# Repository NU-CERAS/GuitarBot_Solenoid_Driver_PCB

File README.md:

KiCAD files for the GuitarBot's Solenoid Driver

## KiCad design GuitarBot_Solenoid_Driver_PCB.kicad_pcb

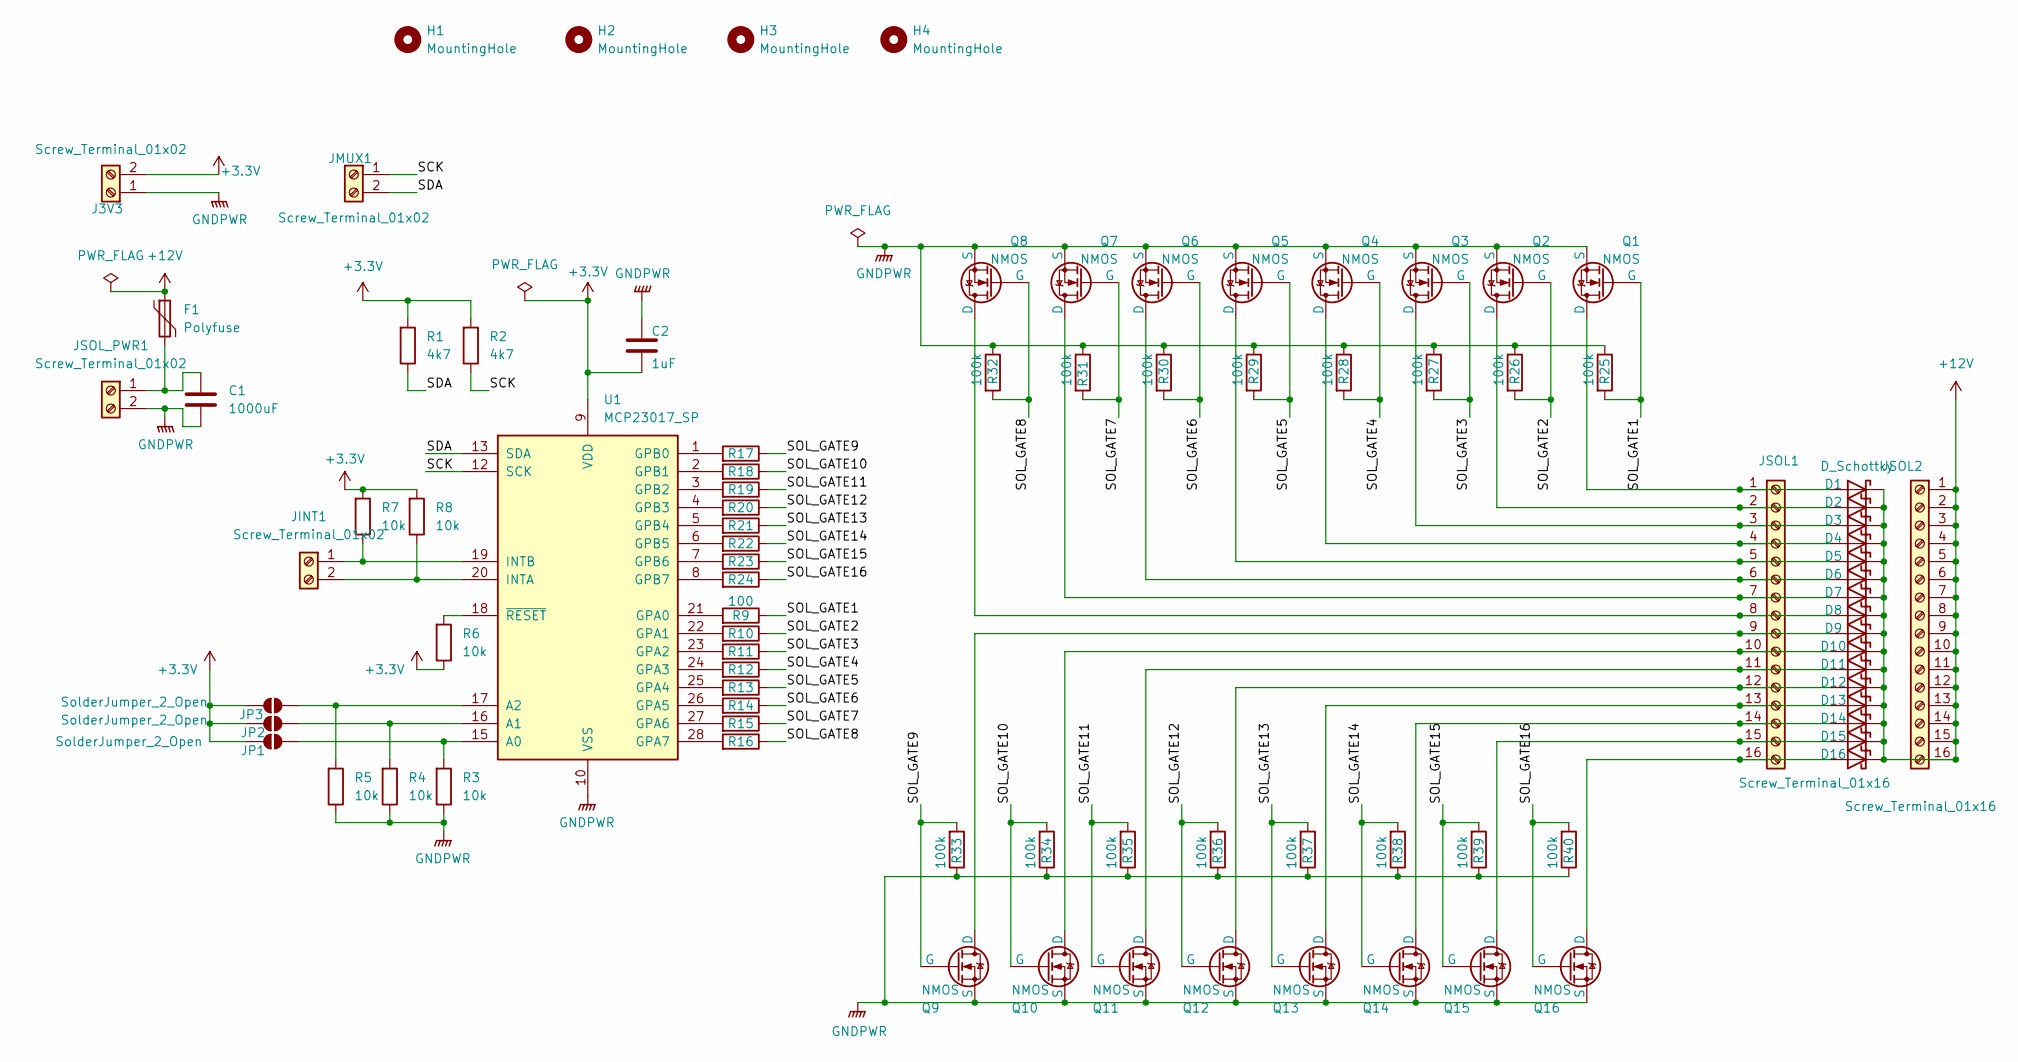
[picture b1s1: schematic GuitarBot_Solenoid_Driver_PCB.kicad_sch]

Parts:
C1: 1000uF; CP_Radial_D10.0mm_P5.00mm
C2: 1uF; C_Radial_D10.0mm_H16.0mm_P5.00mm
D1, D2, D3, D4, D5, D6, D7, D8, D9, D10, D11, D12, D13, D14, D15, D16: D_Schottky; D_DO-201AD_P12.70mm_Horizontal
F1: Polyfuse; C_Disc_D11.0mm_W5.0mm_P5.00mm
H1, H2, H3, H4: MountingHole; MountingHole_3.2mm_M3
J3V3: Screw_Terminal_01x02; TerminalBlock_Xinya_XY308-2.54-2P_1x02_P2.54mm_Horizontal
JINT1: Screw_Terminal_01x02; TerminalBlock_Xinya_XY308-2.54-2P_1x02_P2.54mm_Horizontal
JMUX1: Screw_Terminal_01x02; TerminalBlock_Xinya_XY308-2.54-2P_1x02_P2.54mm_Horizontal
JP1, JP2, JP3: SolderJumper_2_Open; SolderJumper-2_P1.3mm_Open_TrianglePad1.0x1.5mm
JSOL1, JSOL2: Screw_Terminal_01x16; TerminalBlock_CUI_TB007-508-16_1x16_P5.08mm_Horizontal
JSOL_PWR1: Screw_Terminal_01x02; TerminalBlock_MaiXu_MX126-5.0-02P_1x02_P5.00mm
Q1, Q2, Q3, Q4, Q5, Q6, Q7, Q8, Q9, Q10, Q11, Q12, Q13, Q14, Q15, Q16: NMOS; TO-220-3_Vertical
R1, R2: 4k7; R_Axial_DIN0207_L6.3mm_D2.5mm_P7.62mm_Horizontal
R3, R4, R5, R6, R7, R8: 10k; R_Axial_DIN0207_L6.3mm_D2.5mm_P7.62mm_Horizontal
R9, R10, R11, R12, R13, R14, R15, R16, R17, R18, R19, R20, R21, R22, R23, R24: 100; R_Axial_DIN0207_L6.3mm_D2.5mm_P7.62mm_Horizontal
R25, R26, R27, R28, R29, R30, R31, R32, R33, R34, R35, R36, R37, R38, R39, R40: 100k; R_Axial_DIN0207_L6.3mm_D2.5mm_P7.62mm_Horizontal
U1: MCP23017_SP; DIP-28_W7.62mm

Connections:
+3.3V: C2.2, J3V3.2, JP1.1 (A), JP2.1 (A), JP3.1 (A), R1.1, R2.1, R6.2, R7.1, R8.1, U1.9 (VDD)
+12V: D1.1 (K), D2.1 (K), D3.1 (K), D4.1 (K), D5.1 (K), D6.1 (K), D7.1 (K), D8.1 (K), D9.1 (K), D10.1 (K), D11.1 (K), D12.1 (K), D13.1 (K), D14.1 (K), D15.1 (K), D16.1 (K), F1.1, JSOL2.1, JSOL2.2, JSOL2.3, JSOL2.4, JSOL2.5, JSOL2.6, JSOL2.7, JSOL2.8, JSOL2.9, JSOL2.10, JSOL2.11, JSOL2.12, JSOL2.13, JSOL2.14, JSOL2.15, JSOL2.16
/SCK: JMUX1.1, R2.2, U1.12 (SCK)
/SDA: JMUX1.2, R1.2, U1.13 (SDA)
/SOL_GATE1: Q1.1 (G), R9.1, R25.2
/SOL_GATE2: Q2.1 (G), R10.1, R26.2
/SOL_GATE3: Q3.1 (G), R11.1, R27.2
/SOL_GATE4: Q4.1 (G), R12.1, R28.2
/SOL_GATE5: Q5.1 (G), R13.1, R29.2
/SOL_GATE6: Q6.1 (G), R14.1, R30.2
/SOL_GATE7: Q7.1 (G), R15.1, R31.2
/SOL_GATE8: Q8.1 (G), R16.1, R32.2
/SOL_GATE9: Q9.1 (G), R17.1, R33.2
/SOL_GATE10: Q10.1 (G), R18.1, R34.2
/SOL_GATE11: Q11.1 (G), R19.1, R35.2
/SOL_GATE12: Q12.1 (G), R20.1, R36.2
/SOL_GATE13: Q13.1 (G), R21.1, R37.2
/SOL_GATE14: Q14.1 (G), R22.1, R38.2
/SOL_GATE15: Q15.1 (G), R23.1, R39.2
/SOL_GATE16: Q16.1 (G), R24.1, R40.2
GNDPWR: C1.2, C2.1, J3V3.1, JSOL_PWR1.2, Q1.3 (S), Q2.3 (S), Q3.3 (S), Q4.3 (S), Q5.3 (S), Q6.3 (S), Q7.3 (S), Q8.3 (S), Q9.3 (S), Q10.3 (S), Q11.3 (S), Q12.3 (S), Q13.3 (S), Q14.3 (S), Q15.3 (S), Q16.3 (S), R3.2, R4.2, R5.2, R25.1, R26.1, R27.1, R28.1, R29.1, R30.1, R31.1, R32.1, R33.1, R34.1, R35.1, R36.1, R37.1, R38.1, R39.1, R40.1, U1.10 (VSS)
unnamed: D1.2 (A), JSOL1.1, Q1.2 (D)
unnamed: D2.2 (A), JSOL1.2, Q2.2 (D)
unnamed: D3.2 (A), JSOL1.3, Q3.2 (D)
unnamed: D4.2 (A), JSOL1.4, Q4.2 (D)
unnamed: D5.2 (A), JSOL1.5, Q5.2 (D)
unnamed: D6.2 (A), JSOL1.6, Q6.2 (D)
unnamed: D7.2 (A), JSOL1.7, Q7.2 (D)
unnamed: D8.2 (A), JSOL1.8, Q8.2 (D)
unnamed: D9.2 (A), JSOL1.9, Q9.2 (D)
unnamed: D10.2 (A), JSOL1.10, Q10.2 (D)
unnamed: D11.2 (A), JSOL1.11, Q11.2 (D)
unnamed: D12.2 (A), JSOL1.12, Q12.2 (D)
unnamed: D13.2 (A), JSOL1.13, Q13.2 (D)
unnamed: D14.2 (A), JSOL1.14, Q14.2 (D)
unnamed: D15.2 (A), JSOL1.15, Q15.2 (D)
unnamed: D16.2 (A), JSOL1.16, Q16.2 (D)
unnamed: JINT1.1, R7.2, U1.19 (INTB)
unnamed: JINT1.2, R8.2, U1.20 (INTA)
unnamed: JP1.2 (B), R3.1, U1.15 (A0)
unnamed: JP2.2 (B), R4.1, U1.16 (A1)
unnamed: JP3.2 (B), R5.1, U1.17 (A2)
unnamed: C1.1, F1.2, JSOL_PWR1.1
unnamed: R9.2, U1.21 (GPA0)
unnamed: R10.2, U1.22 (GPA1)
unnamed: R11.2, U1.23 (GPA2)
unnamed: R12.2, U1.24 (GPA3)
unnamed: R13.2, U1.25 (GPA4)
unnamed: R14.2, U1.26 (GPA5)
unnamed: R15.2, U1.27 (GPA6)
unnamed: R16.2, U1.28 (GPA7)
unnamed: R17.2, U1.1 (GPB0)
unnamed: R18.2, U1.2 (GPB1)
unnamed: R19.2, U1.3 (GPB2)
unnamed: R20.2, U1.4 (GPB3)
unnamed: R21.2, U1.5 (GPB4)
unnamed: R22.2, U1.6 (GPB5)
unnamed: R23.2, U1.7 (GPB6)
unnamed: R24.2, U1.8 (GPB7)
unnamed: R6.1, U1.18 (~RESET)

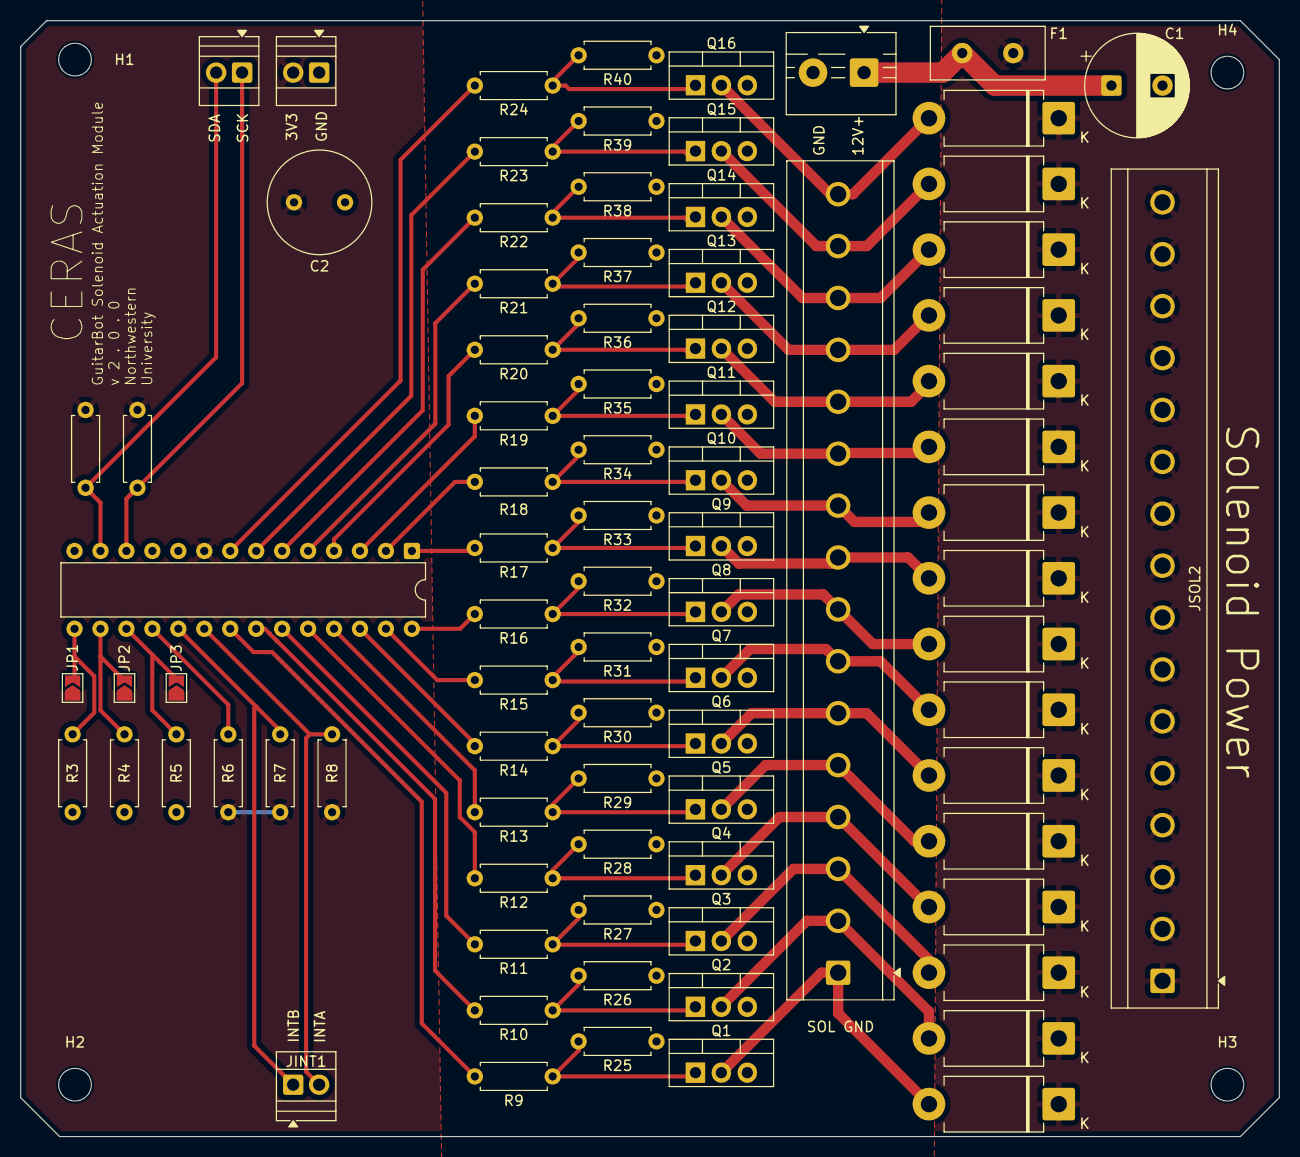
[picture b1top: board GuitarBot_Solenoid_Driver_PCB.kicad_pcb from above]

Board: 2 copper layers, 123.2 x 109.2 mm, 89 parts (0 on the bottom side), 60 nets.

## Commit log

2026-01-06 CMOS schematic complete. Footprints needed
2026-01-11 CMOS array schematic first draft
2026-01-11 modified fp-info-cache
2026-01-18 cmos schematic footprints
2026-01-18 Modified ./old schematic to use NMOS instead of Darlington transistor array
2026-01-29 Added footprints to new board. Switched new and old directories
2026-02-05 Started pcb layout and updated schematic
2026-02-05 Started layout and updated schematic
2026-02-08 Fixed transistors in the schematic and added transistor wiring for PCB
2026-02-12 Fixed NMOS symbol in schematic. Finished wiring the PCB
2026-02-12 cleaned up extra files, added .gitignore
2026-02-12 cleanup
2026-02-15 schematic: interrupt and reset pulldown, NMOS gate pulldown, fuses on 12V and 3V3
2026-02-22 Finished feb15 updates to layout
2026-02-26 made wired farther apart
2026-03-05 initial schematics for ilya rennovations
2026-03-05 Finished up the layout, it passes DRC but idk how good it looks
2026-04-05 Fixed connectection issue with resistors
2026-04-09 Switched to 5.08mm 01x16 terminal blocks
2026-04-09 changed 01x16 terminal blocks from 2.54mm to 5.08mm
2026-04-09 Minimal changes to naming
2026-04-12 Added labelling for inputs and outputs
2026-04-12 Reverted NMOS footprint to 220-3. Rearranged terminalblocks to fit accordingly.
2026-04-12 changed polyfuse footprint
2026-04-12 fixed labels:
2026-04-16 fixed traces
2026-04-16 moved text
